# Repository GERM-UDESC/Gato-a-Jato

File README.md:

# LineFollower
Seguidor de linha

Projeto de TCC de Engenharia Elétrica do aluno Bruno Luiz Demarchi, sob orientação do professor Douglas Wildgrube Bertol.

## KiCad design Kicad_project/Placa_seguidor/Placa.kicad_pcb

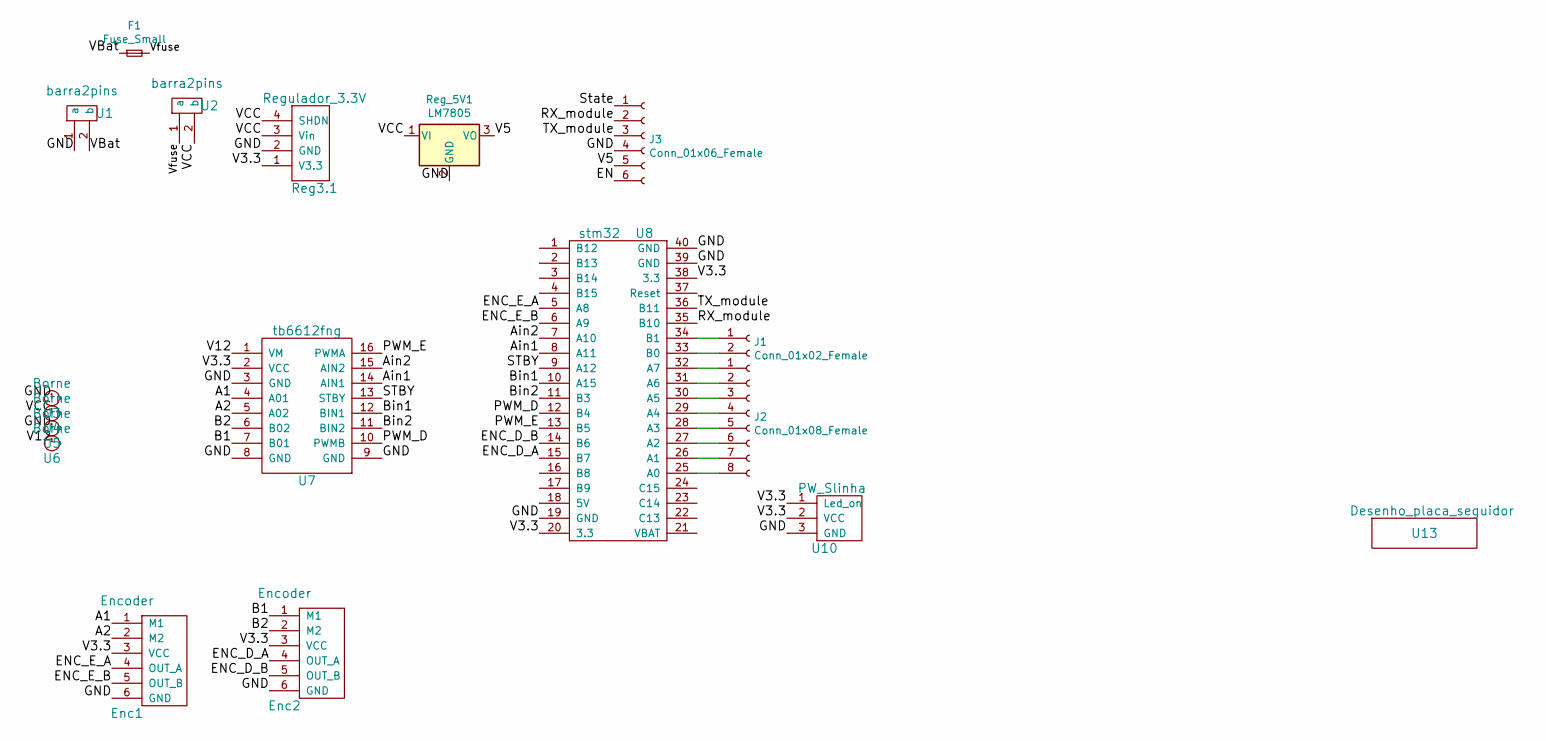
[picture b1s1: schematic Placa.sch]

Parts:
Enc1, Enc2: Encoder
F1: Fuse_Small; R_Axial_DIN0309_L9.0mm_D3.2mm_P5.08mm_Vertical
J1: Conn_01x02_Female; PinSocket_1x02_P2.54mm_Vertical
J2: Conn_01x08_Female; PinSocket_1x08_P2.54mm_Vertical
J3: Conn_01x06_Female; PinSocket_1x06_P2.54mm_Vertical
Reg3.1: Regulador_3.3V
Reg_5V1: LM7805; TO-220-3_Vertical
U1, U2: barra2pins
U3, U4, U5, U6: Borne
U7: tb6612fng
U8: stm32
U10: PW_Slinha
U13: Desenho_placa_seguidor; Desenho_Nova_Placa_Seguidor

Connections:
/A1: Enc1.1 (M1), U7.4 (A01)
/A2: Enc1.2 (M2), U7.5 (A02)
/Ain1: U7.14 (AIN1), U8.8 (A11)
/Ain2: U7.15 (AIN2), U8.7 (A10)
/B1: Enc2.1 (M1), U7.7 (B01)
/B2: Enc2.2 (M2), U7.6 (B02)
/Bin1: U7.12 (BIN1), U8.10 (A15)
/Bin2: U7.11 (BIN2), U8.11 (B3)
/EN: J3.6
/ENC_D_A: Enc2.4 (OUT_A), U8.15 (B7)
/ENC_D_B: Enc2.5 (OUT_B), U8.14 (B6)
/ENC_E_A: Enc1.4 (OUT_A), U8.5 (A8)
/ENC_E_B: Enc1.5 (OUT_B), U8.6 (A9)
/GND: Enc1.6 (GND), Enc2.6 (GND), J3.4, Reg3.1.2 (GND), Reg_5V1.2 (GND), U1.1 (a), U3.1, U5.1, U7.3 (GND), U7.8 (GND), U7.9 (GND), U8.19 (GND), U8.39 (GND), U8.40 (GND), U10.3 (GND)
/PWM_D: U7.10 (PWMB), U8.12 (B4)
/PWM_E: U7.16 (PWMA), U8.13 (B5)
/RX_module: J3.2, U8.35 (B10)
/STBY: U7.13 (STBY), U8.9 (A12)
/State: J3.1
/TX_module: J3.3, U8.36 (B11)
/V3.3: Enc1.3 (VCC), Enc2.3 (VCC), Reg3.1.1 (V3.3), U7.2 (VCC), U8.20 (3.3), U8.38 (3.3), U10.1 (Led_on), U10.2 (VCC)
/V5: J3.5, Reg_5V1.3 (VO)
/V12: U6.1, U7.1 (VM)
/VBat: F1.1, U1.2 (b)
/VCC: Reg3.1.3 (Vin), Reg3.1.4 (SHDN), Reg_5V1.1 (VI), U2.2 (b), U4.1
/Vfuse: F1.2, U2.1 (a)
unnamed: J1.1, U8.34 (B1)
unnamed: J1.2, U8.33 (B0)
unnamed: J2.1, U8.32 (A7)
unnamed: J2.2, U8.31 (A6)
unnamed: J2.3, U8.30 (A5)
unnamed: J2.4, U8.29 (A4)
unnamed: J2.5, U8.28 (A3)
unnamed: J2.6, U8.27 (A2)
unnamed: J2.7, U8.26 (A1)
unnamed: J2.8, U8.25 (A0)

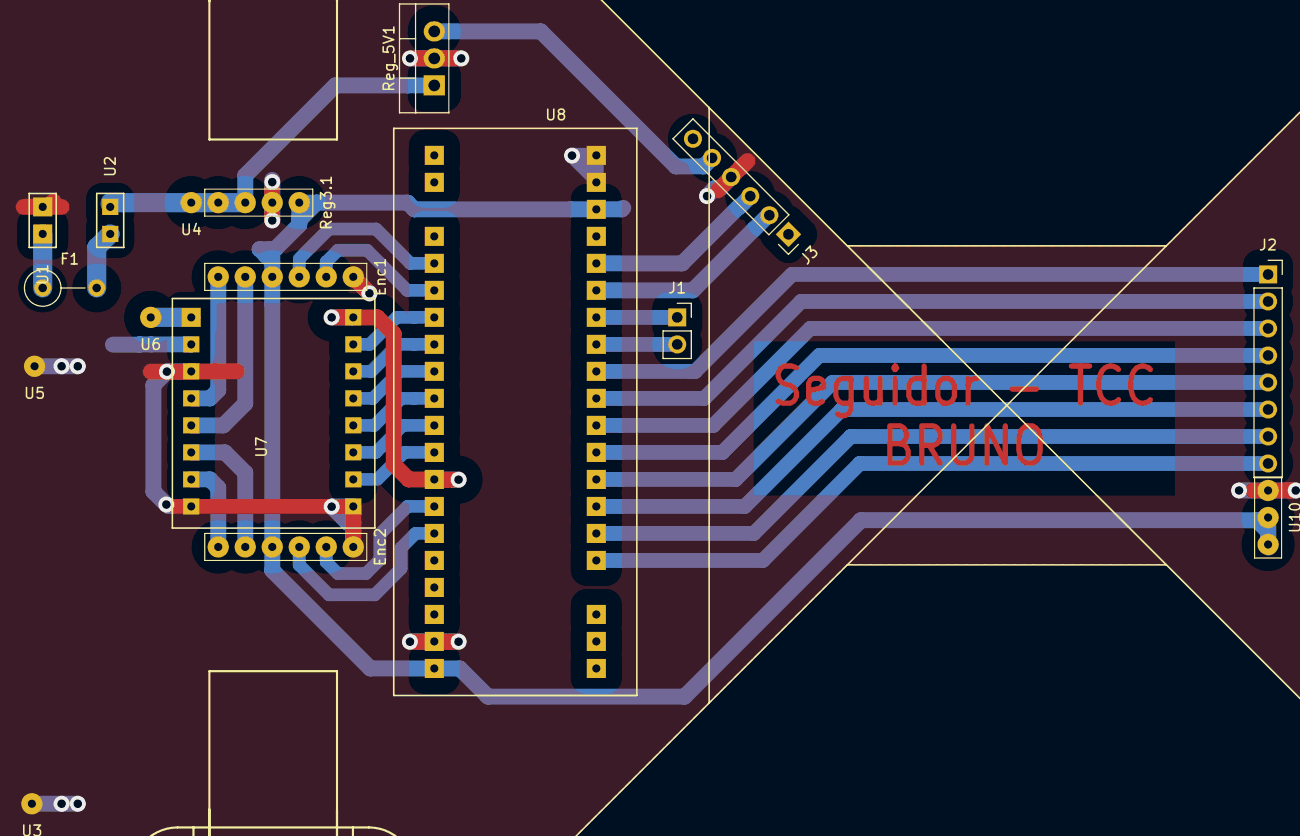
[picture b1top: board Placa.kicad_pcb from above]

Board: 2 copper layers, 18 parts (0 on the bottom side), 34 nets.

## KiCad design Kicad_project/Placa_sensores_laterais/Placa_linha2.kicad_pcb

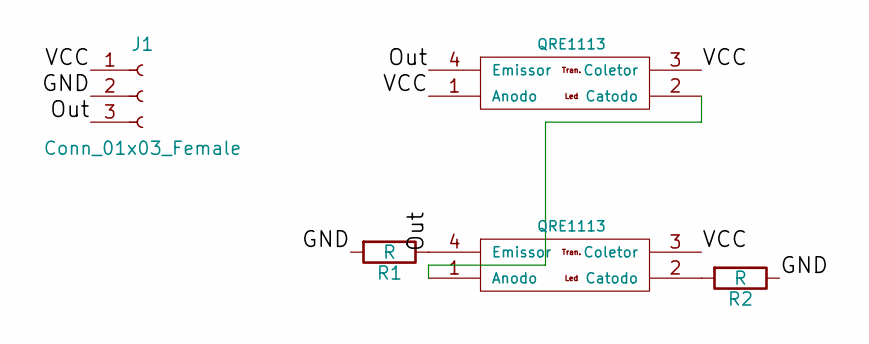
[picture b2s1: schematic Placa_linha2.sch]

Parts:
J1: Conn_01x03_Female; barra3pins
R1, R2: R; R_Axial_DIN0207_L6.3mm_D2.5mm_P2.54mm_Vertical
U1, U3: QRE1113; QRE1113_SMD

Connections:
/GND: J1.2, R1.2, R2.1
/Out: J1.3, R1.1, U1.4 (Emissor), U3.4 (Emissor)
/VCC: J1.1, U1.1 (Anodo), U1.3 (Coletor), U3.3 (Coletor)
unnamed: R2.2, U3.2 (Catodo)
unnamed: U1.2 (Catodo), U3.1 (Anodo)

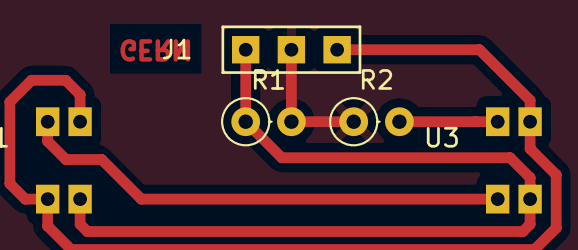
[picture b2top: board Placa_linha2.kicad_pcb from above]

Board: 2 copper layers, 5 parts (0 on the bottom side), 5 nets.

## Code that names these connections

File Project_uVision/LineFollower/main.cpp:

#include "Micro.h"
#include "SysClock.h"
#include "GPIO.h"
#include "TIMER.h"
#include "PWM.h"
#include "ENCODER.h"
#include "ADC.h"
#include "REFLECTANCE_SENSOR.h"
#include "LINE_SENSOR.h"
#include "MOTOR.h"
#include "USART.h"
#include "KINEMATIC_CONTROL.h"
#include "FOLLOWING_CONTROLER.h"
#include "SERIAL_COMMUNICATION.h"

#include "math.h"

float xtest, ytest, vtest, wtest;
float linevalue, lineangle;
float time, delta_time, dtencd, dtence;
uint8_t test_serial;


int main()
{
//	NVIC->IP[TIM1_UP_IRQn] = 1;
//	NVIC->IP[TIM4_IRQn] = 2;
//	NVIC->IP[TIM3_IRQn] = 3;
	//-----------------------------------Initiallize static parameters----------------------
	Timer::Timer_Initiallize();
	Encoder::Encoder_Initiallize();
	Motor::Motor_Initialiize();
	
	//----------------------------------------Setup----------------------------------------
	SysClock Board;		//initiallize the board clock
	
	//Board LED
	GPIO LED_Board(PC13, GP_OUTPUT_PUSH_PULL_2MHZ);
	
	//Timer
	Timer Time_Generator(TIM2, COUNTER); //This one is dedicated to generate the time base in useconds
	
	//H bridge configuration
	GPIO STBY(PA12, GP_OUTPUT_PUSH_PULL_2MHZ);
	GPIO AIN2(PA10, GP_OUTPUT_PUSH_PULL_2MHZ);
	GPIO AIN1(PA11, GP_OUTPUT_PUSH_PULL_2MHZ);
	GPIO BIN1(PA15, GP_OUTPUT_PUSH_PULL_2MHZ);
	GPIO BIN2(PB3, GP_OUTPUT_PUSH_PULL_2MHZ);
	AIN2.digitalWrite(LOW);
	AIN1.digitalWrite(LOW);
	BIN2.digitalWrite(LOW);
	BIN1.digitalWrite(LOW);
	STBY.digitalWrite(HIGH);				
		
	//PWM configurations
	PWM PWM_E(TIM3, TIM_CH2, PARTIAL_REMAP2);
	PWM PWM_D(TIM3, TIM_CH1, PARTIAL_REMAP2);
	PWM_E.PWMWrite(0);
	PWM_D.PWMWrite(0);
	
	//Encoders configuration
	Encoder ENC_E(TIM1);
	Encoder ENC_D(TIM4);
	
	//Motor configuration
	Motor Motor_E(PWM_E, ENC_E, AIN2, AIN1);
	Motor Motor_D(PWM_D, ENC_D, BIN1, BIN2);
	
	//Line sensor
	Reflectance_Sensor Sensor1(ADC_CH0);
	Reflectance_Sensor Sensor2(ADC_CH1);
	Reflectance_Sensor Sensor3(ADC_CH2);
	Reflectance_Sensor Sensor4(ADC_CH3);
	Reflectance_Sensor Sensor5(ADC_CH4);
	Reflectance_Sensor Sensor6(ADC_CH5);
	Reflectance_Sensor Sensor7(ADC_CH6);
	Reflectance_Sensor Sensor8(ADC_CH7);
	Line_Sensor Sensor_Board(Sensor1, Sensor2, Sensor3, Sensor4, Sensor5, Sensor6, Sensor7, Sensor8);
	
	//Robot Kinematic
	Kinematic Robot(Motor_D, Motor_E, Sensor_Board);
	
	//Robot Control
	Controller RobotControl(Robot);
	
	//Serial communication
	USART Serial(USART3, BD_1382400);
	
	Communication Interface(&RobotControl, &Serial);
	
	//----------------------------------------------------------------------------------------------
	
	//----------------------------------Initial Conditions------------------------------------------
	STBY.digitalWrite(HIGH);

	//-----------------------------------------------------------------------------------------------

	RobotControl.Robot.reset();
	RobotControl.stop();
	LED_Board.tooglePin();
	RobotControl.Robot.calibrateLineSensor(100000);
	LED_Board.tooglePin();
	while (Timer::GetTime_usec() < 10000000);
	RobotControl.start(v_ref_ini, 0);
//	Interface.waitForCommand();
	
	while(1)
	{
//		linevalue = RobotControl.Robot.getLinePosition();
//		lineangle = RobotControl.Robot.getLineAngle();
//		xtest = RobotControl.Robot.deltaDistance;
//		vtest = RobotControl.Robot.getV();
//		wtest = RobotControl.Robot.getW();
//		xtest = RobotControl.Robot.motorD.encoder.getSpeed();
//		ytest = RobotControl.Robot.motorE.encoder.getSpeed();
//    test_serial = Interface.command;
		if (Timer::verifyTimeInterrupt())
		{
//			time = Timer::GetTime_usec();
			Encoder::Encoder_Handler_by_Time();
			Motor::Motor_Handler_by_time();
			Kinematic::handlerByTime();
			Controller::HandlerByTime();
//			Communication::HandlerByTime();
//			delta_time = Timer::GetTime_usec() - time;
		}
		if (Timer::GetTime_usec() > 37500000) RobotControl.stop();
//		if (Timer::GetTime_usec() > 18000000) RobotControl.setSpeedRef(1,0);
//		if (Timer::GetTime_usec() > 24000000) RobotControl.setSpeedRef(0.8,0);			
		if ((Board.SysTickGetEvent()) && (Interface.command != robotStop))
		{
			LED_Board.tooglePin();
		}
	}
}


//Interruption Part

//Encoder 1 - Interrupt Handler			//Encoder Esquerdo
extern "C" void TIM1_UP_IRQHandler();
//Encoder 2 - Interrupt Handler			//this timer is being used as time base for the system
extern "C" void TIM2_IRQHandler();
//Encoder 3 - Interrupt Handler			//PWM generator
extern "C" void TIM3_IRQHandler();
//Encoder 4 - Interrupt Handler			//Encoder direito
extern "C" void TIM4_IRQHandler();

void TIM1_UP_IRQHandler()
{
	TIM1->SR &= ~(1<<0);
	Encoder::Encoder_Handler(Encoder_TIM1);
};

void TIM2_IRQHandler()
{
	TIM2->SR &= ~(1<<0);
	Timer::Timer_Handler();
};

void TIM3_IRQHandler()
{
	TIM3->SR &= ~(1<<0);
};

void TIM4_IRQHandler()
{
	TIM4->SR &= ~(1<<0);
	Encoder::Encoder_Handler(Encoder_TIM4);
};

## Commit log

2018-09-24 Alterado o arquivo de README
2018-09-24 Lista de funções a serem implementadas
2018-09-24 include driver class
2018-09-29 Project created in uVison 5
2018-09-29 just excluding some trashes
2018-09-29 I've deleted these files without knowing, just put it back again
2018-10-08 Inclusion of a project written in C++ I've just "translated" from C to C++
2018-10-09 removed old C project, updated to C++
2018-10-09 changes on GPIO class
2018-10-09 changes on main to adequate the GPIO class changes
2018-10-26 Included Timer and PWM classes
    There are a lot of modifications due to a problem to open gitkraken and stage the smaller modifications
2018-10-26 Organizing the files
2018-10-26 Added Getters and Setters to GPIO class
2018-10-27 Added Getters and Setter to Timer class
2018-10-27 Updates
    I've made some modifications all over the code to make it easyer to be readable and used.
    I've also figured why pin PA15, PB3 and PB4 were not working. By default the MCU configure this pins to be used with a JTAG, but as I'm using only St-link and i'll need these pins as PWM in my projec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
2018-10-27 Added ADC.h and ADC.cpp
    I've included just these files but I didn't implement anything on these.
    I've just implemented a ADC code in main.c that works
2018-10-27 Implemented ADC reading
    ADCRead from CH0 to CH9 (PA0 -PB1) are working.
    I've put some code at main. The code basically blink the board LED while read a potentiometer and write a PWM value at 4 LEDs
2018-10-28 Implemented Quadrature Encoder
2018-10-29 Upgrades in the GPIO
2018-10-31 A lot of updates
    Upgraded the input paramenters in GPIO, insted of using "GPIOx" and "PINy" as input, we can know use "Pxy"
    I've also removed the inherence of timer, now timer isn't a child of GPIO and because of that I had to update all the others drivers too
2018-11-02 Implemented Timer Interrupt and it's handler
    i've also made some tests to get the motor speed in main C, its working but now I have to implement it in a driver
2019-01-02 A lot of implementations
2019-01-11 Testing reflectance sensor
    Worked fine
2019-01-23 Line sensor working
2019-01-23 Class Motor finished
    need some tests now
2019-01-30 almost there
    all drivers are working, the only one that is not working yet is the motor class
2019-02-05 some tests
2019-02-24 Included USART driver
    Included just some basic definitions for USART driver, but it's far from working
2019-02-26 UART WORKING
    the sending and receiving by UART is working
2019-02-26 Script to aquire motor speed and send
    It's working, but, I'll have to change the way that the encoder driver calculate the speed
2019-02-27 encoder aprimorated and sample app too
2019-02-27 some upgrades
2019-02-27 Encoder driver updated
    Now, the interrupts are generated at every 2 ticks, which is the minimum possible, and at each interrupt, the speed and position of the respective encoder is updated
2019-02-28 Encoder and USART drivers updated
    Added a handler_by_time in Encoder driver and added the 57600 baud rate to usart
2019-02-28 Fixed some problems with the PWM driver
2019-03-01 everything finished (i guess)
2019-03-05 Updated USART driver with new clocks
2019-03-11 Implemented Motor control
    Implemented Motor control and added matlab simulation
2019-03-16 Implemented communication with matlab
2019-03-17 Interrupts updated
2019-03-18 another changes
2019-03-23 Include Kinematic control
    I've also updated some stuffs to fixes negative speeds
2019-03-23 some math error fixed
2019-03-25 included some extra functions to Kinematic
2019-03-26 sending float over serial implemented
2019-04-18 some changes
2019-04-19 Escrita do tcc
2019-05-26 Kanayama control implemented in matlab
2019-05-31 Kanayama Control working
    I coudn't test the angle reading, so I don't know if it's right, but in general, it's working
2019-07-30 Implemented another control rules
2019-08-10 Some tests to fix angle reading
2019-08-15 some updates
2019-08-22 working on an interface
2019-08-23 working on an interface yet
    also fixed some line reading problems
2019-08-28 Serial communication almost working 100%
2019-08-30 it seems to be working now
2019-09-17 incremented encoder resolution
    implemented some filters at speed, line and angle reading
2019-09-28 Some filters and position mapping implemented
2019-10-20 Updated matlab script
2019-11-09 communication updates
2019-11-10 fixed some errors
    fixed getAngle equation error and get x,y too
